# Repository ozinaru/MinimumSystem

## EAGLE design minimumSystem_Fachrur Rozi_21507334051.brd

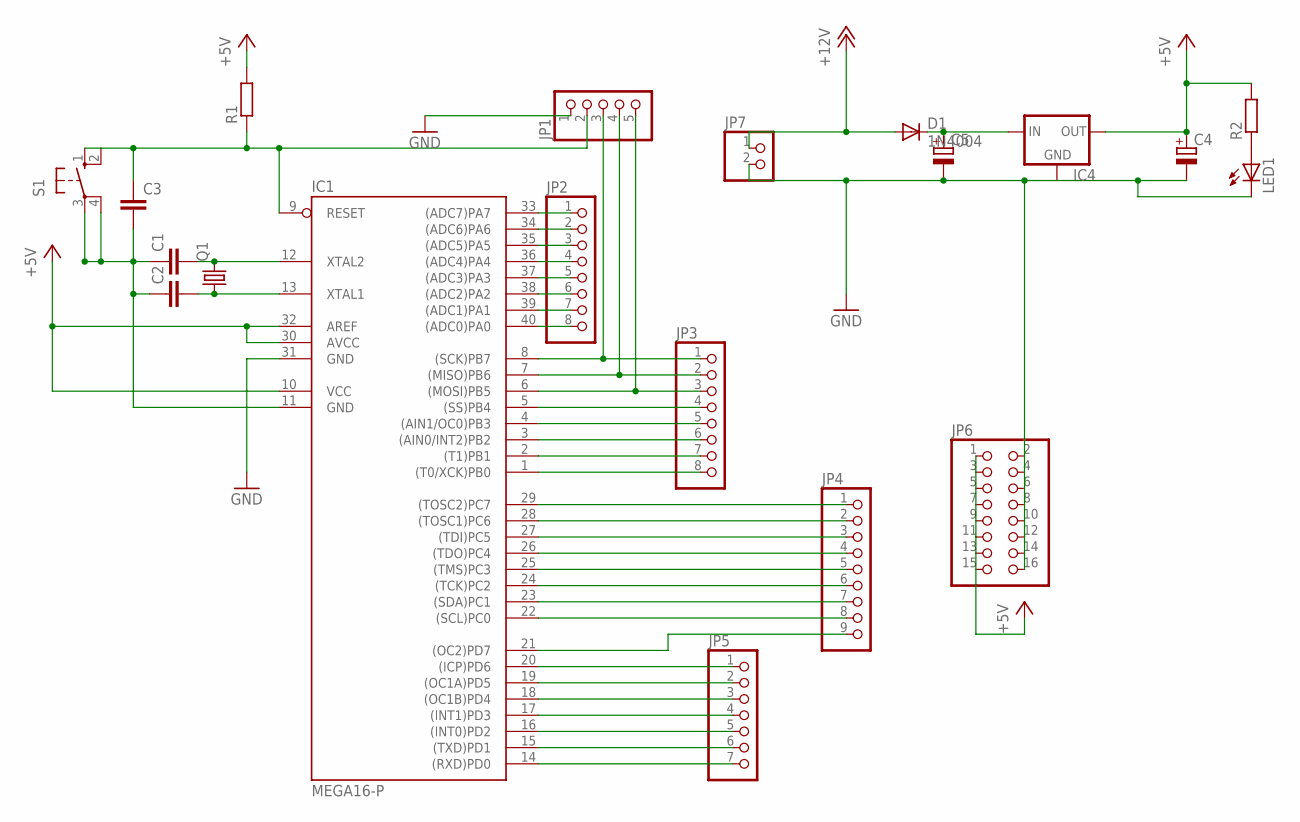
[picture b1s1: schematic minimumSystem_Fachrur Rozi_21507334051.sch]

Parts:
C1, C2: C-EU025-024X044; C025-024X044
C3: C-EU050-025X075; C050-025X075
C4, C5: CPOL-EUE2.5-5; E2,5-5
D1: 1N4004; DO41-10
IC1: MEGA16-P; DIL40
IC4: 78XXS
JP1: PINHD-1X5; 1X05
JP2, JP3: PINHD-1X8; 1X08
JP4: PINHD-1X9; 1X09
JP5: PINHD-1X7; 1X07
JP6: PINHD-2X8; 2X08
JP7: PINHD-1X2; 1X02
LED1: LED5MM
Q1: CRYSTALHC49U-V; HC49U-V
R1, R2: R-EU_0204/7; 0204/7
S1: 10-XX; B3F-10XX

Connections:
+5V: C4.+, IC1.10 (VCC), IC1.30 (AVCC), IC1.32 (AREF), IC4.OUT, JP6.1, JP6.3, JP6.5, JP6.7, JP6.9, JP6.11, JP6.13, JP6.15, R1.2, R2.2
+12V: D1.A, JP7.1
C0: IC1.22 ((SCL)PC0), JP4.8
C1: IC1.23 ((SDA)PC1), JP4.7
C2: IC1.24 ((TCK)PC2), JP4.6
C3: IC1.25 ((TMS)PC3), JP4.5
D7: IC1.14 ((RXD)PD0), JP5.7
GND: C1.1, C2.1, C3.2, C4.-, C5.-, IC1.11 (GND), IC1.31 (GND), IC4.GND, JP1.1, JP6.2, JP6.4, JP6.6, JP6.8, JP6.10, JP6.12, JP6.14, JP6.16, JP7.2, LED1.K (C), S1.3, S1.4 (P1)
unnamed: IC1.33 ((ADC7)PA7), JP2.1
unnamed: IC1.34 ((ADC6)PA6), JP2.2
unnamed: IC1.35 ((ADC5)PA5), JP2.3
unnamed: IC1.36 ((ADC4)PA4), JP2.4
unnamed: IC1.37 ((ADC3)PA3), JP2.5
unnamed: IC1.38 ((ADC2)PA2), JP2.6
unnamed: IC1.39 ((ADC1)PA1), JP2.7
unnamed: IC1.40 ((ADC0)PA0), JP2.8
unnamed: IC1.29 ((TOSC2)PC7), JP4.1
unnamed: IC1.28 ((TOSC1)PC6), JP4.2
unnamed: IC1.27 ((TDI)PC5), JP4.3
unnamed: IC1.5 ((SS)PB4), JP3.4
unnamed: IC1.20 ((ICP)PD6), JP5.1
unnamed: IC1.19 ((OC1A)PD5), JP5.2
unnamed: IC1.26 ((TDO)PC4), JP4.4
unnamed: IC1.6 ((MOSI)PB5), JP1.5, JP3.3
unnamed: IC1.4 ((AIN1/OC0)PB3), JP3.5
unnamed: IC1.3 ((AIN0/INT2)PB2), JP3.6
unnamed: IC1.2 ((T1)PB1), JP3.7
unnamed: IC1.1 ((T0/XCK)PB0), JP3.8
unnamed: C5.+, D1.C, IC4.IN
unnamed: IC1.15 ((TXD)PD1), JP5.6
unnamed: IC1.16 ((INT0)PD2), JP5.5
unnamed: IC1.17 ((INT1)PD3), JP5.4
unnamed: C3.1, IC1.9 (RESET), JP1.2, R1.1, S1.1 (S), S1.2 (S1)
unnamed: IC1.18 ((OC1B)PD4), JP5.3
unnamed: C1.2, IC1.12 (XTAL2), Q1.2
unnamed: C2.2, IC1.13 (XTAL1), Q1.1
unnamed: LED1.A, R2.1
unnamed: IC1.8 ((SCK)PB7), JP1.3, JP3.1
unnamed: IC1.7 ((MISO)PB6), JP1.4, JP3.2
RS: IC1.21 ((OC2)PD7), JP4.9

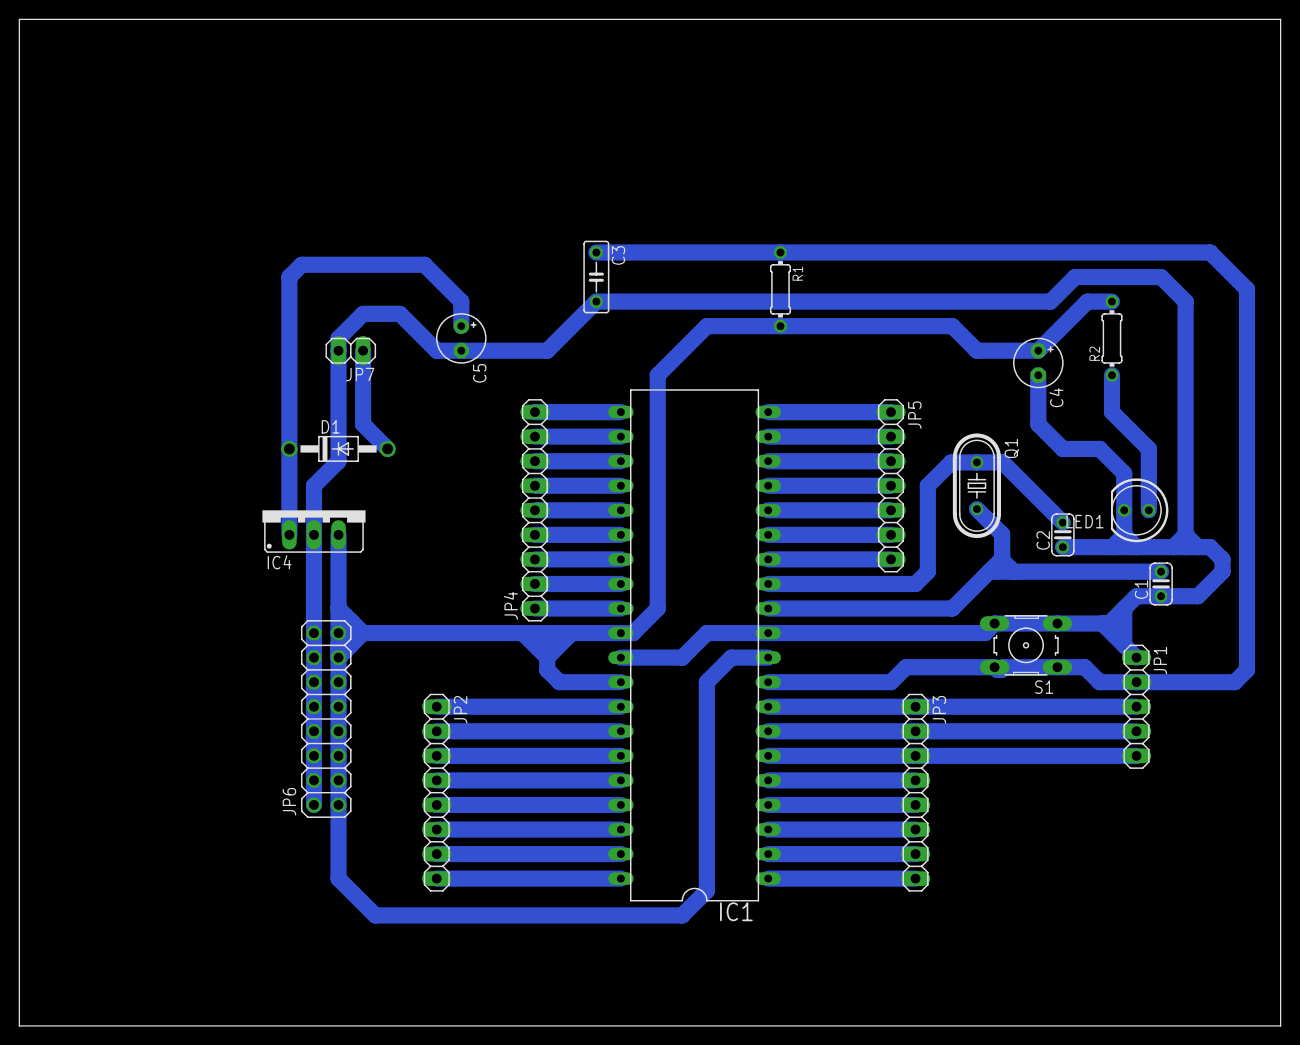
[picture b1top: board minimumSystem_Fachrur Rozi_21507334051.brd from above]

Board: 2 copper layers, 130.5 x 104.1 mm, 20 parts (0 on the bottom side), 40 nets.
